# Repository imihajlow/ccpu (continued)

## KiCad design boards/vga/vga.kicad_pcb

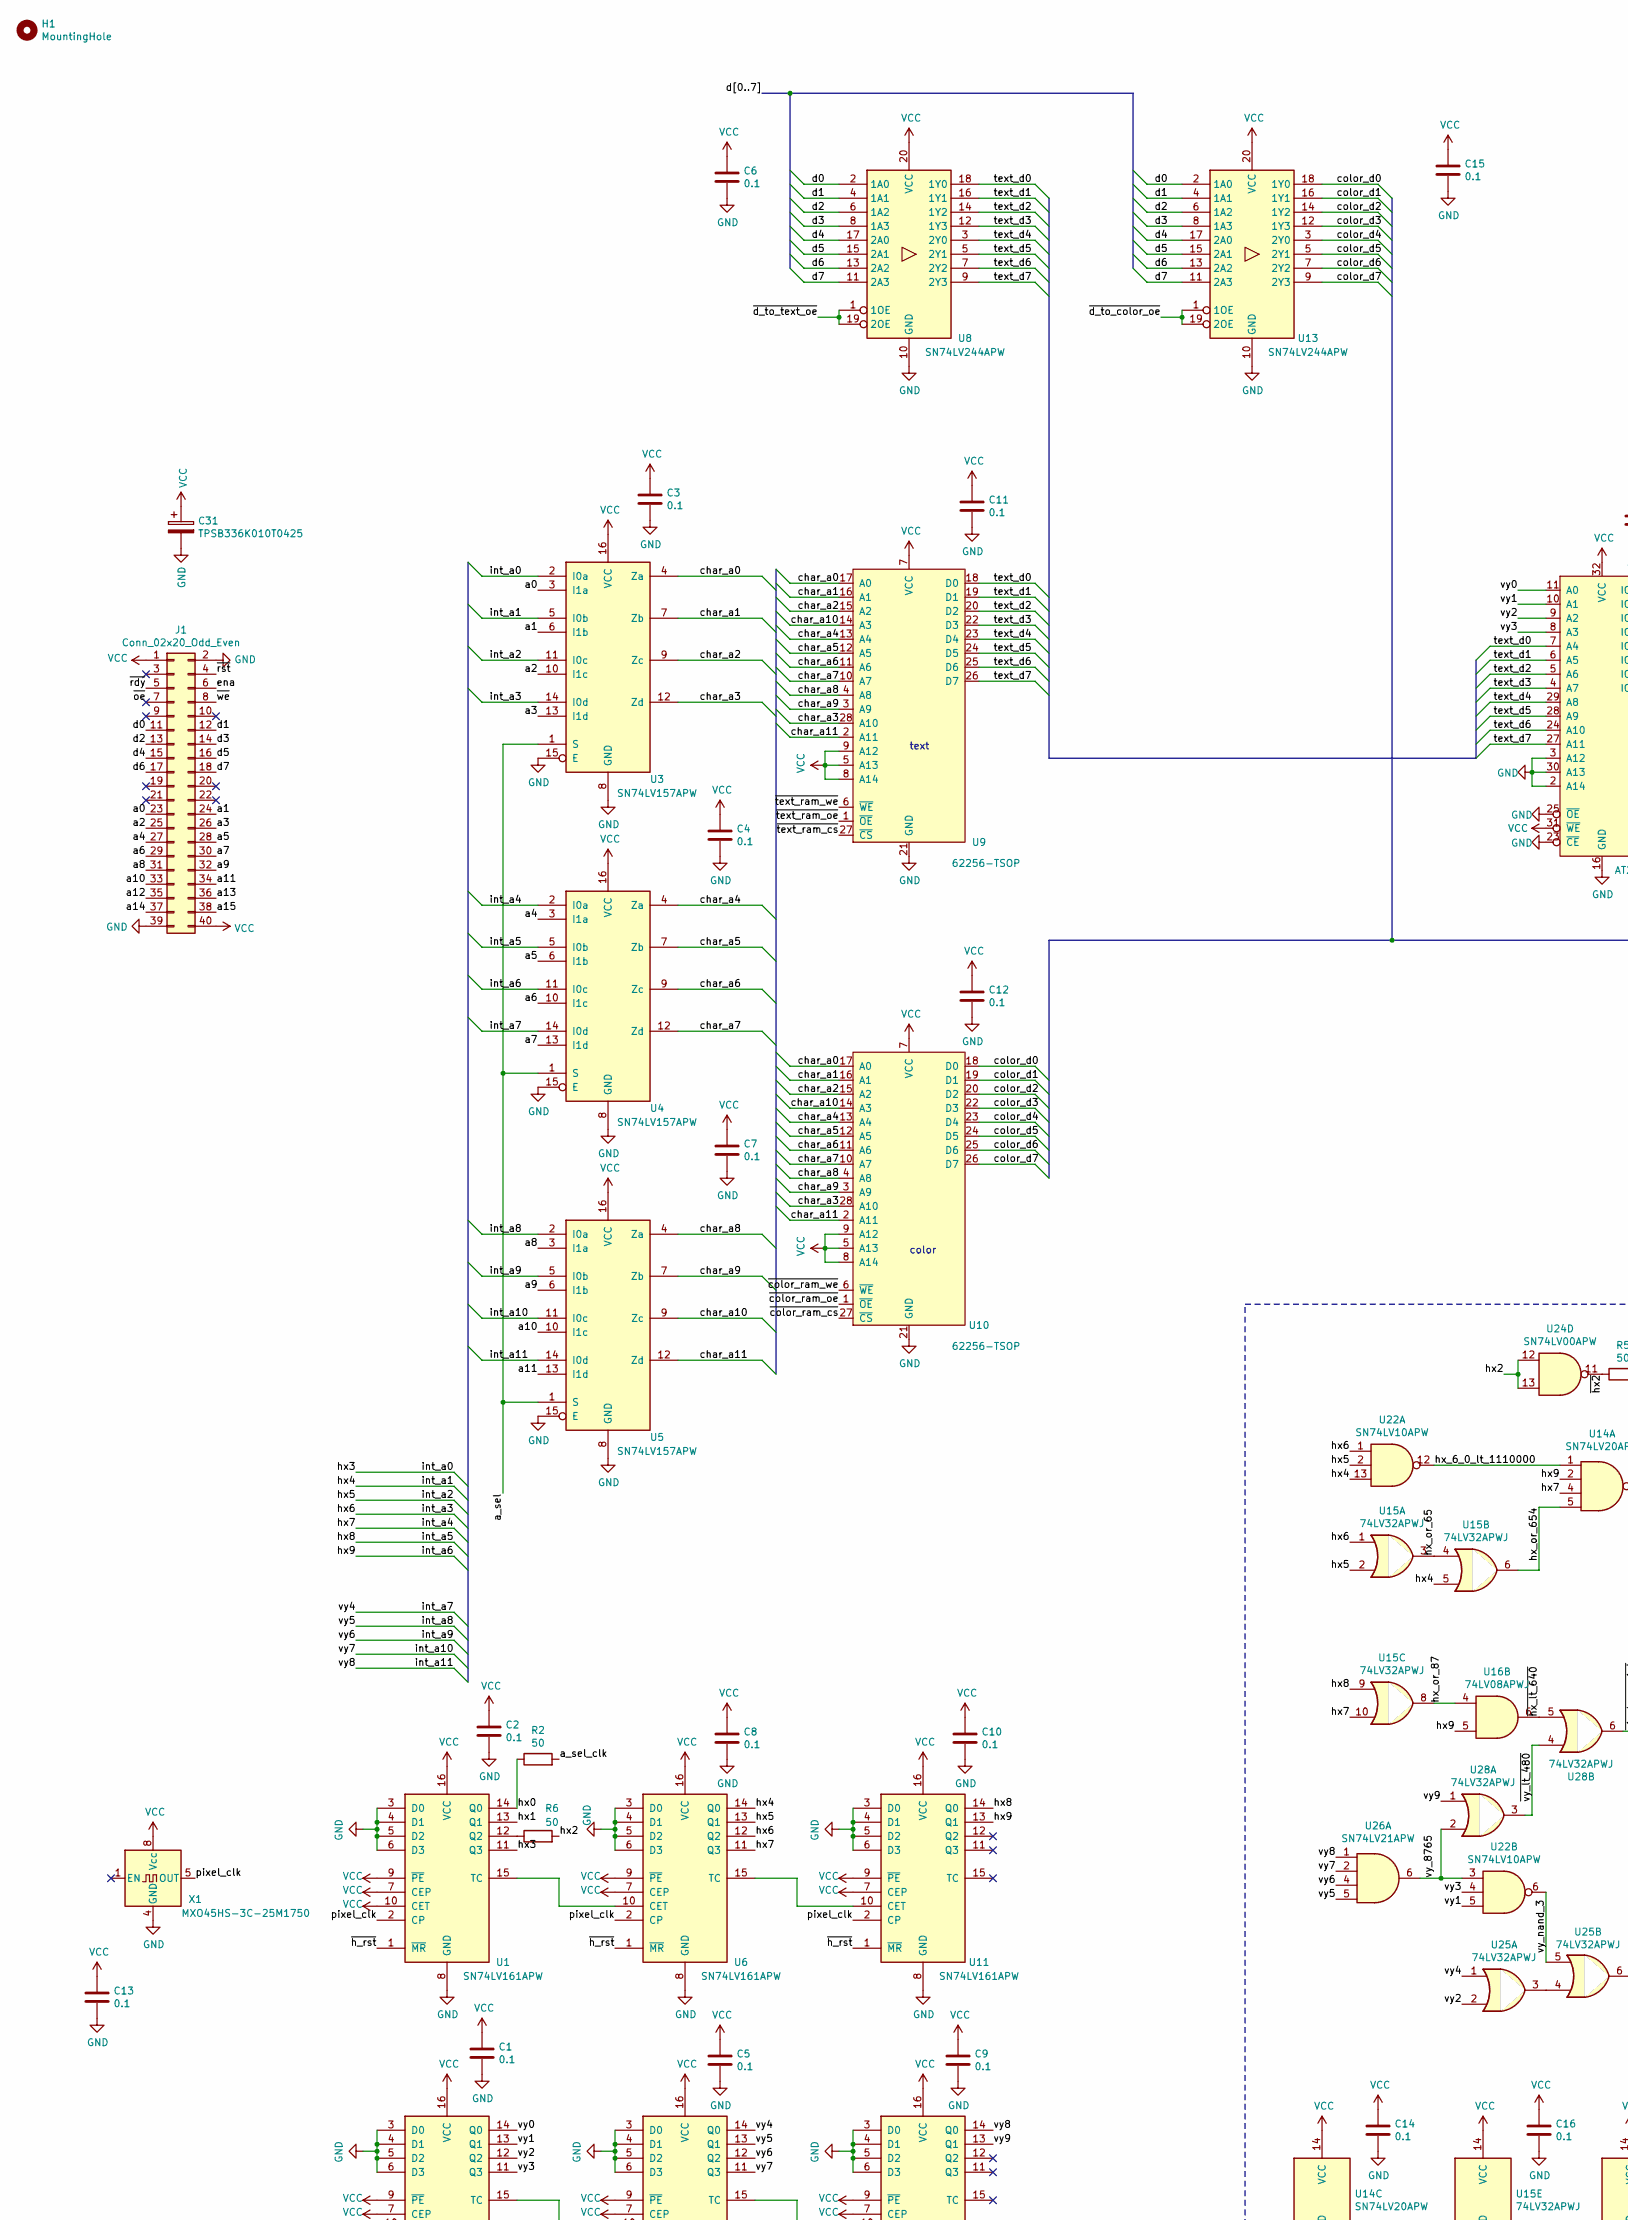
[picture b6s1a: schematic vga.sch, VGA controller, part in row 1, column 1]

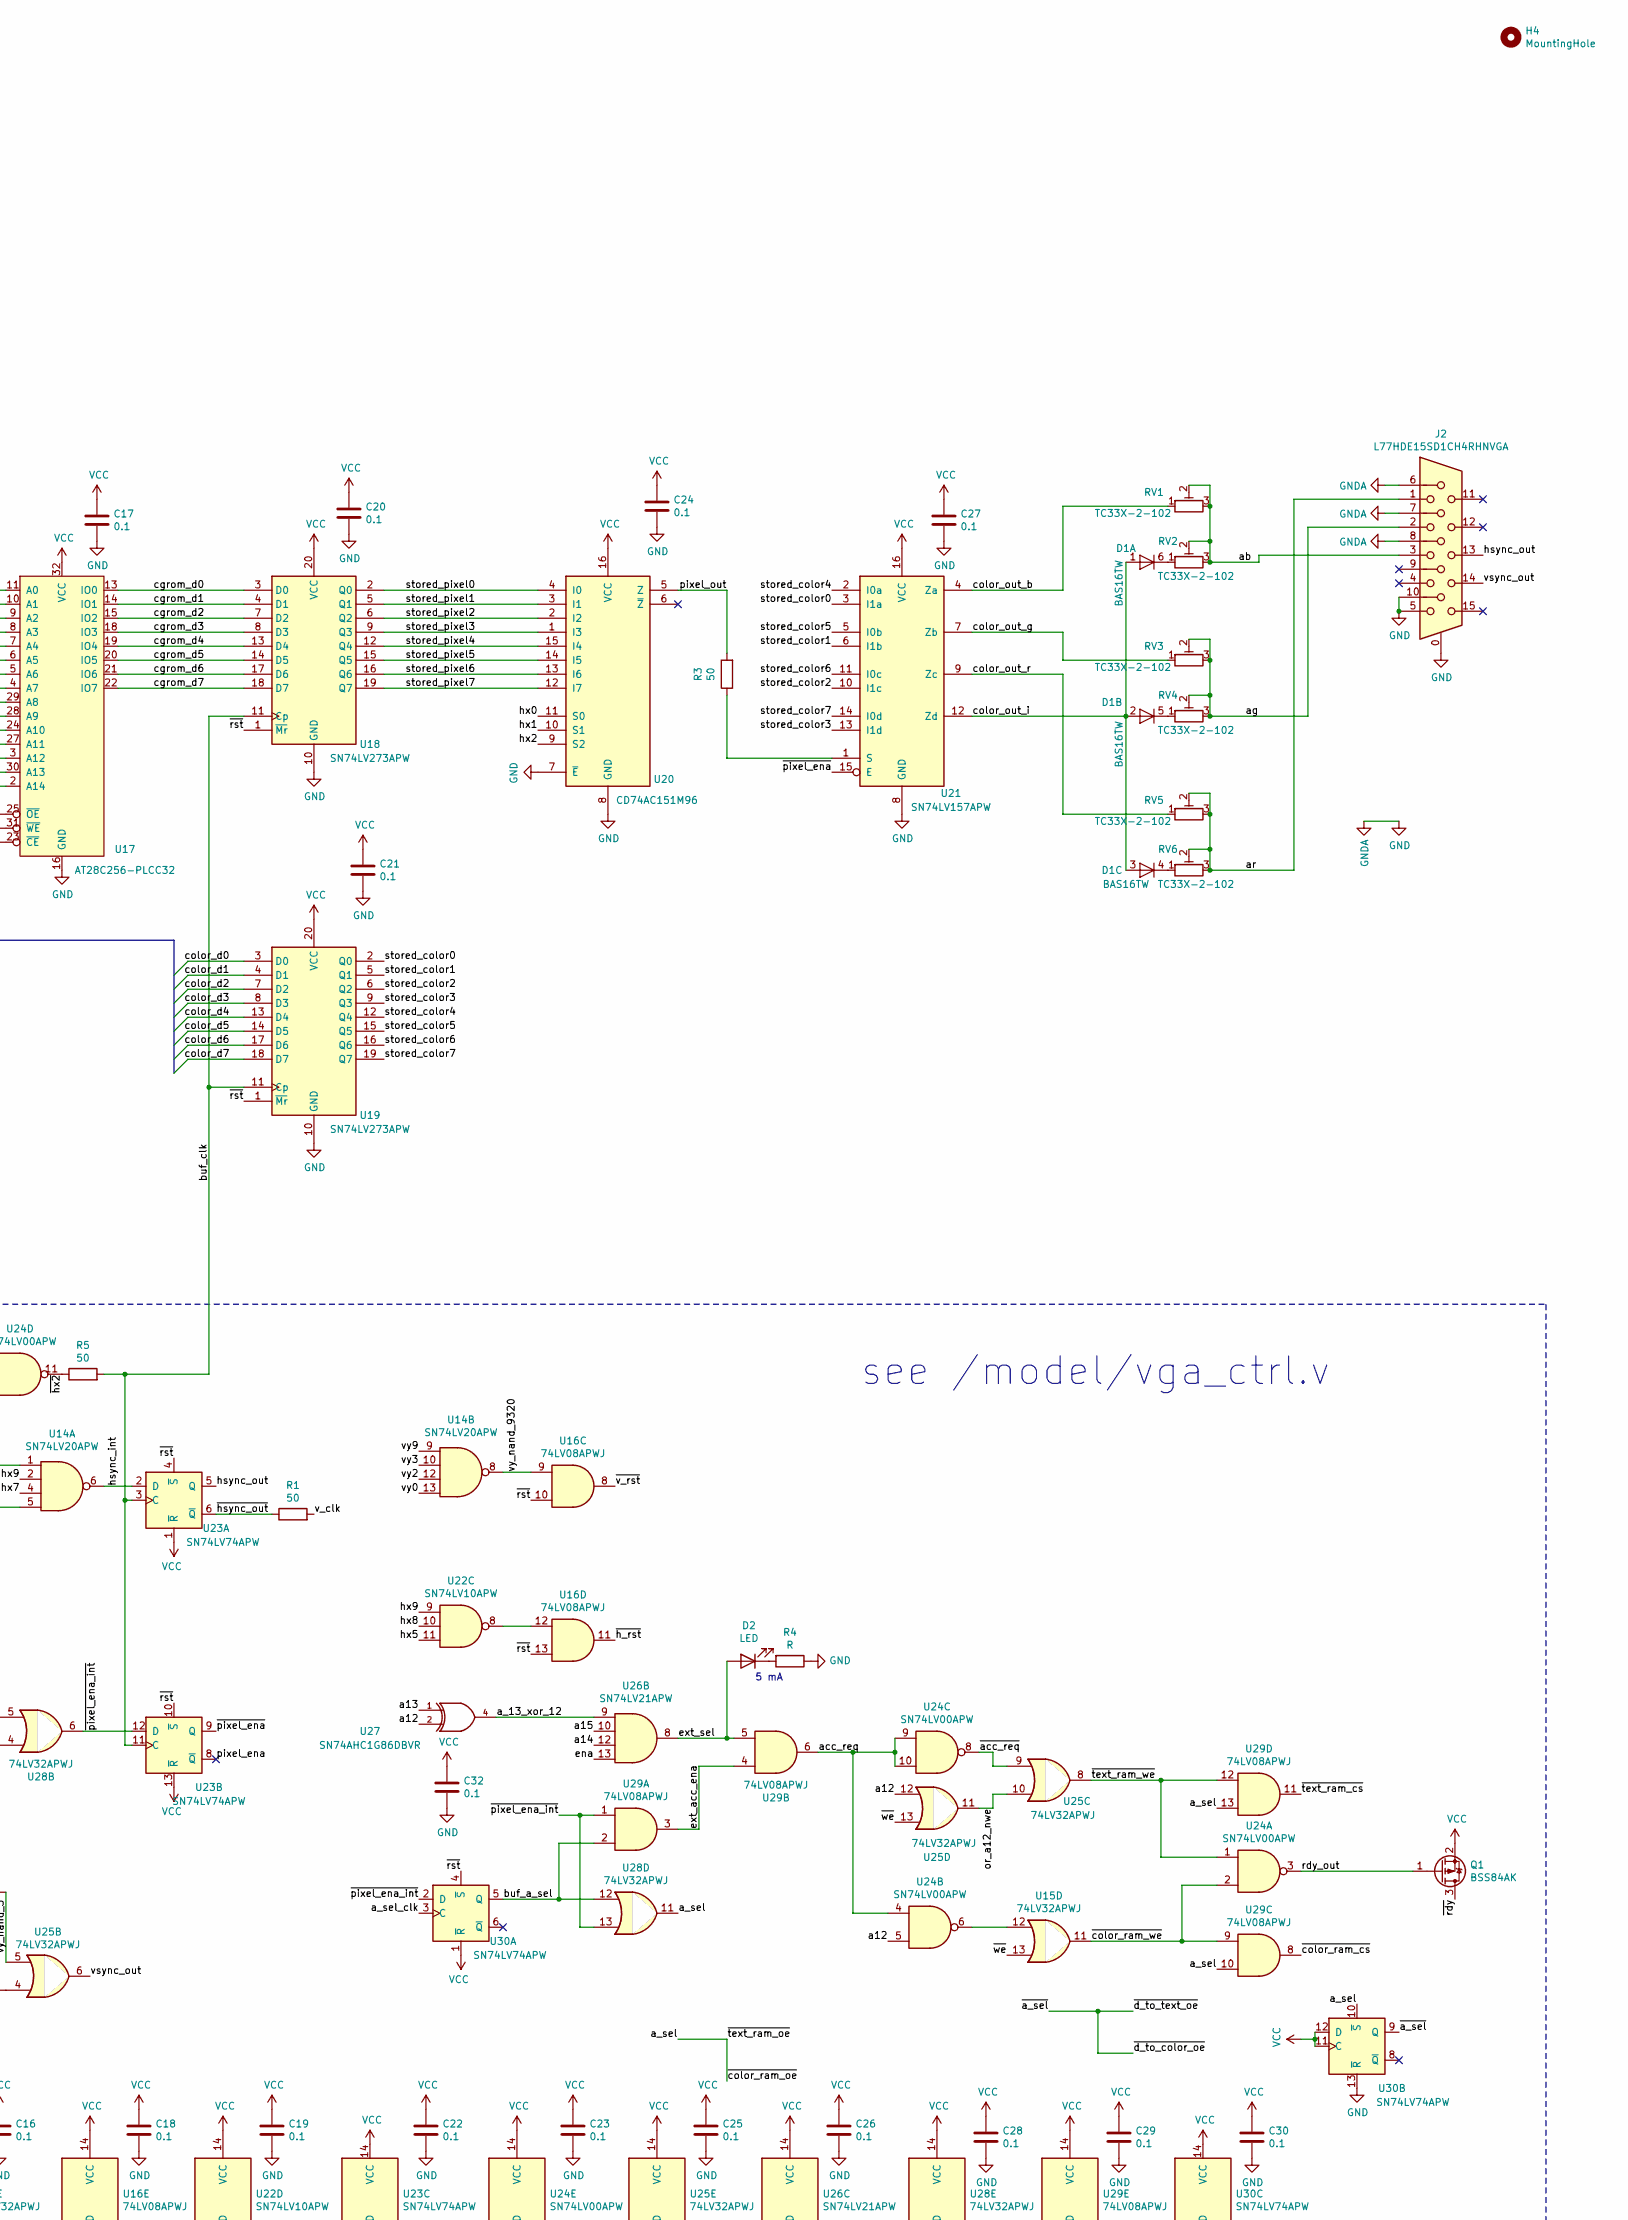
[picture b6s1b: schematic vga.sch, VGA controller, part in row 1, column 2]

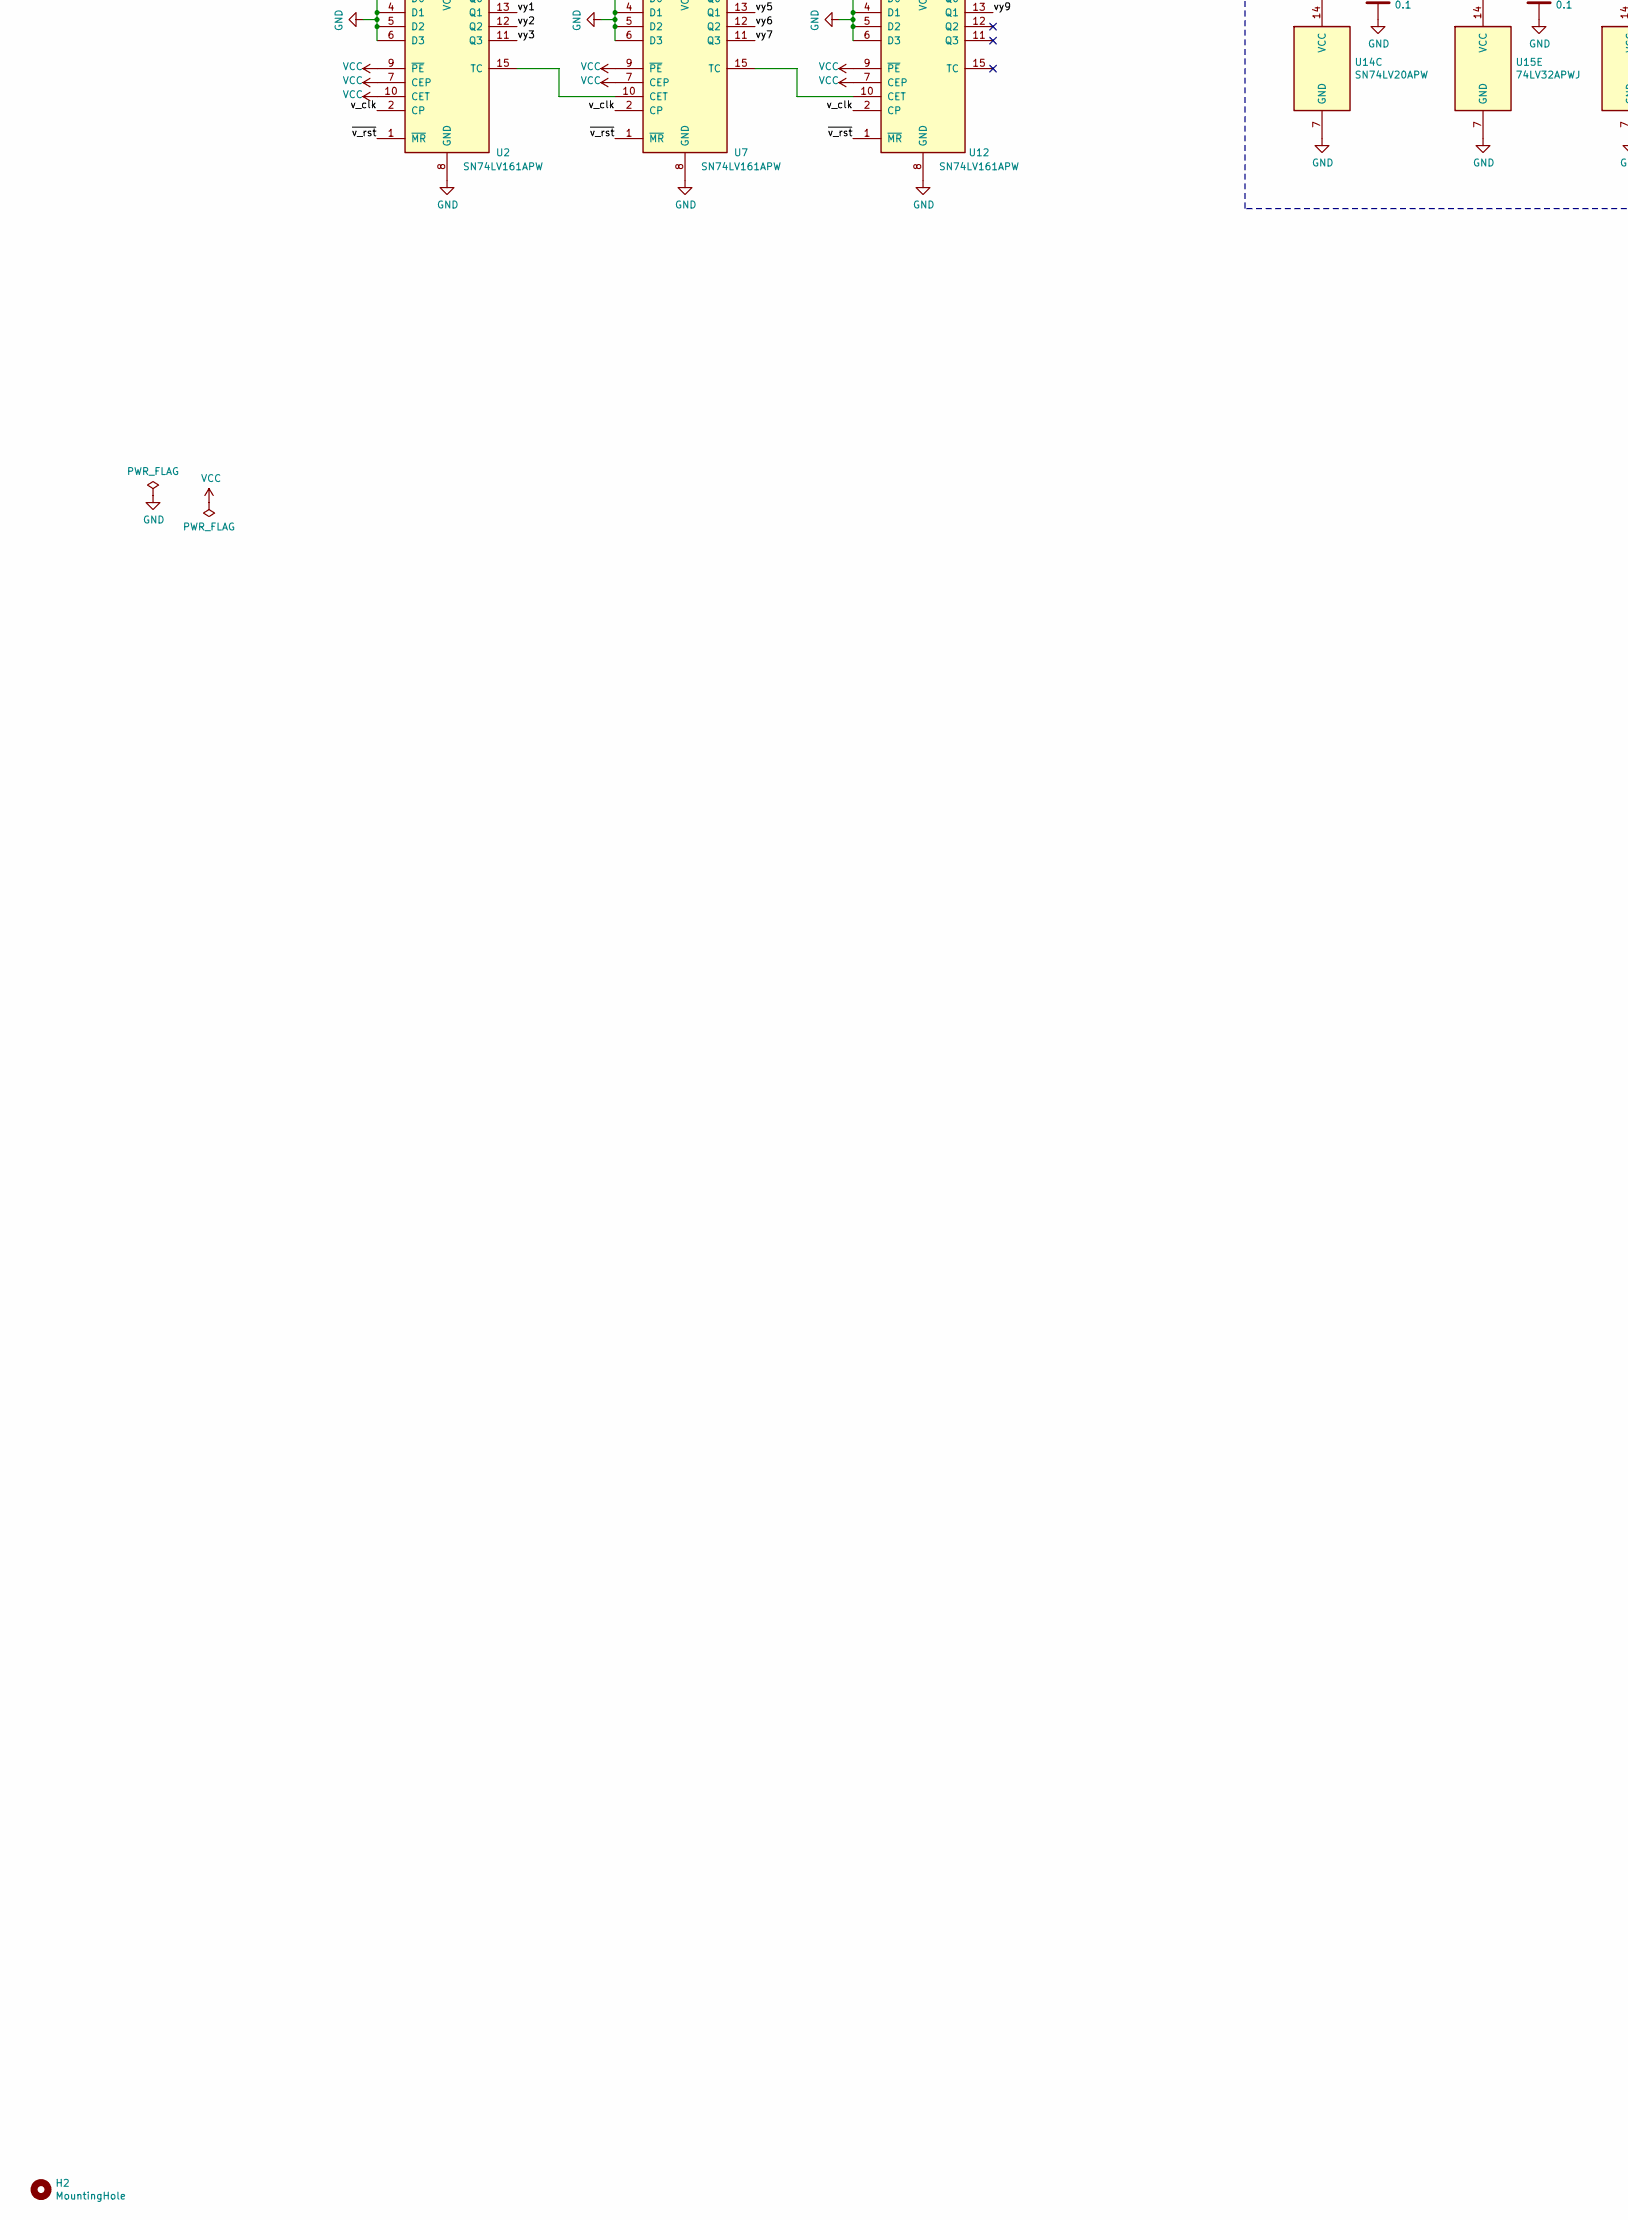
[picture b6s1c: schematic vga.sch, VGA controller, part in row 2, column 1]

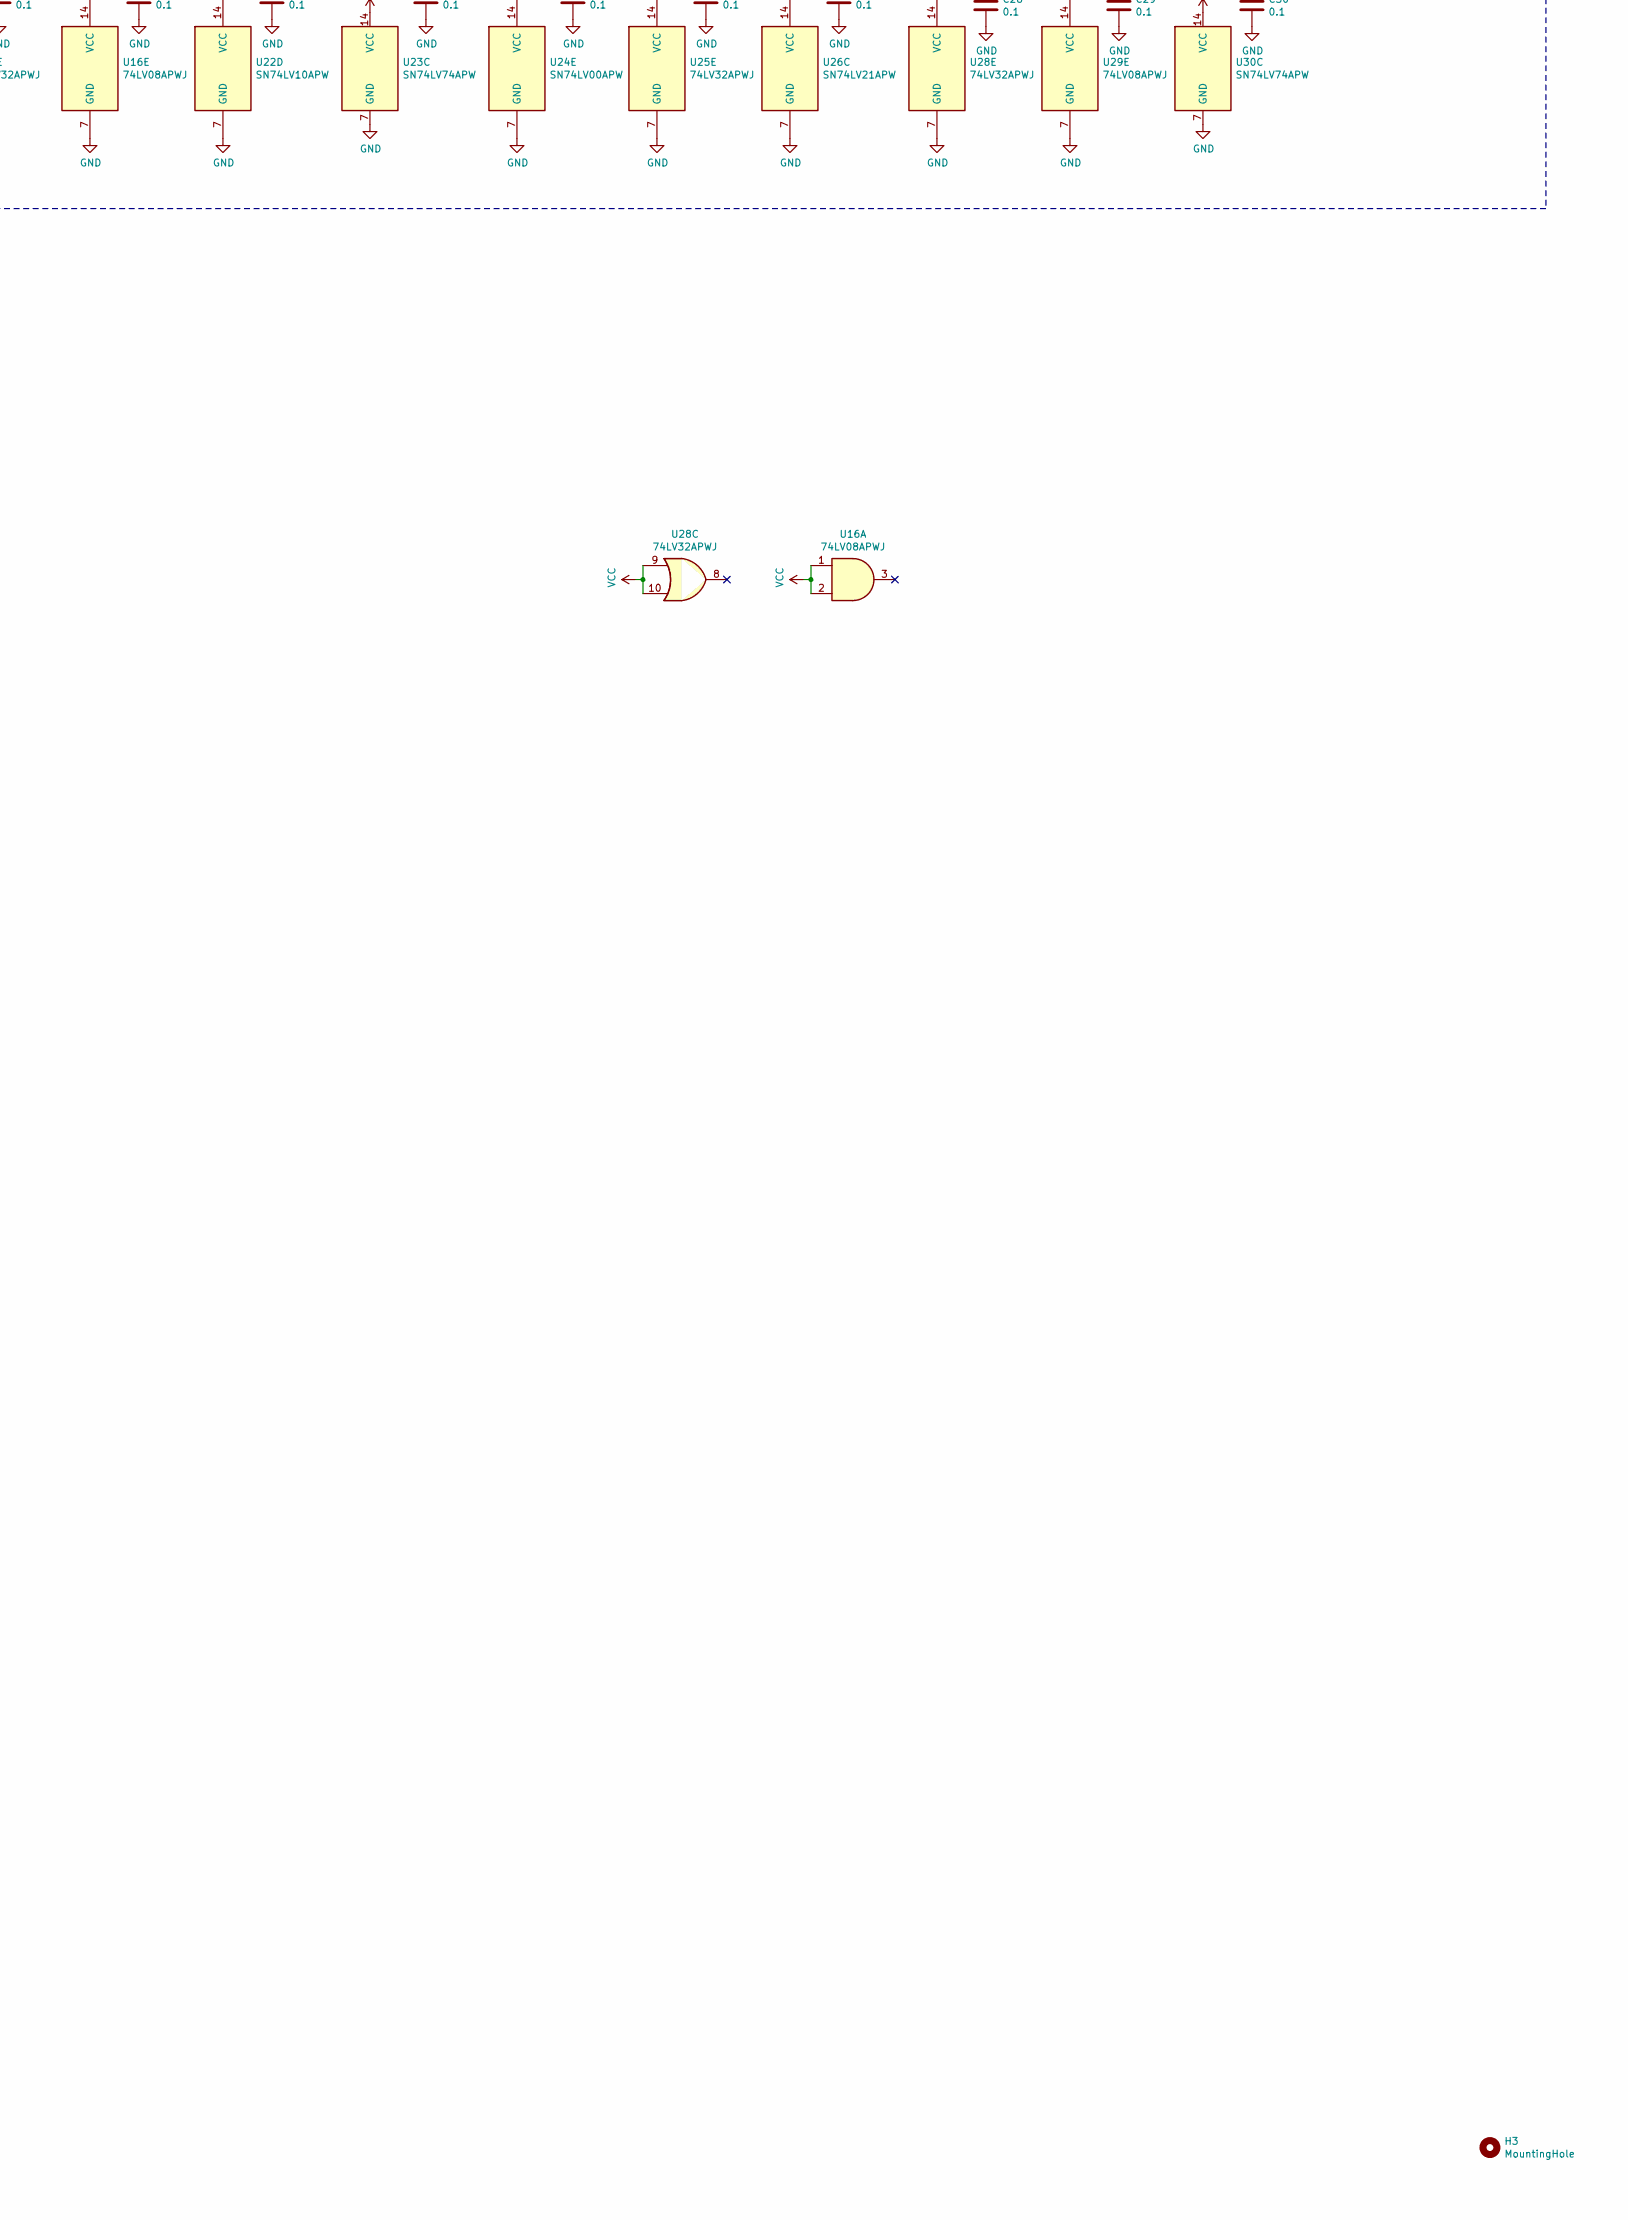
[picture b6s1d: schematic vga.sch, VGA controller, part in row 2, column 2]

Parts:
C1, C2, C3, C4, C5, C6, C7, C8, C9, C10, C11, C12, C13, C14, C15, C16, C17, C18, C19, C20, C21, C22, C23, C24, C25, C26, C27, C28, C29, C30, C32: 0.1; C_0805_2012Metric
C31: TPSB336K010T0425; CP_EIA-3528-15_AVX-H_Pad1.50x2.35mm_HandSolder
D1: BAS16TW; SOT-363_SC-70-6
D2: LED; LED_0805_2012Metric
H1, H2, H3, H4: MountingHole; MountingHole_3.2mm_M3
J1: Conn_02x20_Odd_Even; PinHeader_2x20_P2.54mm_Horizontal
J2: L77HDE15SD1CH4RHNVGA; DSUB-15-HD_Female_Horizontal_P2.29x1.98mm_EdgePinOffset8.35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
Q1: BSS84AK; SOT-23
R1, R2, R3, R5, R6: 50; R_0805_2012Metric
R4: R; R_0805_2012Metric
RV1, RV2, RV3, RV4, RV5, RV6: TC33X-2-102; Potentiometer_Bourns_TC33X_Vertical
U1, U2, U6, U7, U11, U12: SN74LV161APW; TSSOP-16_4.4x5mm_P0.65mm
U3, U4, U5, U21: SN74LV157APW; TSSOP-16_4.4x5mm_P0.65mm
U8, U13: SN74LV244APW; TSSOP-20_4.4x6.5mm_P0.65mm
U9, U10: 62256-TSOP; TSOP-I-28_11.8x8mm_P0.55mm
U14: SN74LV20APW; TSSOP-14_4.4x5mm_P0.65mm
U15, U25, U28: 74LV32APWJ; TSSOP-14_4.4x5mm_P0.65mm
U16, U29: 74LV08APWJ; TSSOP-14_4.4x5mm_P0.65mm
U17: AT28C256-PLCC32; PLCC-32_SMD_Socket
U18, U19: SN74LV273APW; TSSOP-20_4.4x6.5mm_P0.65mm
U20: CD74AC151M96; SOIC-16_3.9x9.9mm_P1.27mm
U22: SN74LV10APW; TSSOP-14_4.4x5mm_P0.65mm
U23, U30: SN74LV74APW; TSSOP-14_4.4x5mm_P0.65mm
U24: SN74LV00APW; TSSOP-14_4.4x5mm_P0.65mm
U26: SN74LV21APW; TSSOP-14_4.4x5mm_P0.65mm
U27: SN74AHC1G86DBVR; SOT-23-5
X1: MXO45HS-3C-25M1750; Oscillator_DIP-8

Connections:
/a0: J1.23, U3.3 (I1a)
/a1: J1.24, U3.6 (I1b)
/a2: J1.25, U3.10 (I1c)
/a3: J1.26, U3.13 (I1d)
/a4: J1.27, U4.3 (I1a)
/a5: J1.28, U4.6 (I1b)
/a6: J1.29, U4.10 (I1c)
/a7: J1.30, U4.13 (I1d)
/a8: J1.31, U5.3 (I1a)
/a9: J1.32, U5.6 (I1b)
/a10: J1.33, U5.10 (I1c)
/a11: J1.34, U5.13 (I1d)
/a12: J1.35, U24.5, U25.12, U27.2
/a13: J1.36, U27.1
/a14: J1.37, U26.12
/a15: J1.38, U26.10
/a_13_xor_12: U26.9, U27.4
/a_sel: U3.1 (S), U4.1 (S), U5.1 (S), U9.1 (~OE), U10.1 (~OE), U28.11, U29.10, U29.13, U30.10 (~S)
/a_sel_clk: R2.2, U30.3 (C)
/ab: J2.3, RV1.2, RV1.3, RV2.2, RV2.3
/acc_req: U24.4, U24.9, U24.10, U29.6
/ag: J2.2, RV3.2, RV3.3, RV4.2, RV4.3
/ar: J2.1, RV5.2, RV5.3, RV6.2, RV6.3
/buf_a_sel: U28.12, U29.2, U30.5 (Q)
/buf_clk: R5.2, U18.11 (Cp), U19.11 (Cp), U23.3 (C), U23.11 (C)
/cgrom_d0: U17.13 (IO0), U18.3 (D0)
/cgrom_d1: U17.14 (IO1), U18.4 (D1)
/cgrom_d2: U17.15 (IO2), U18.7 (D2)
/cgrom_d3: U17.18 (IO3), U18.8 (D3)
/cgrom_d4: U17.19 (IO4), U18.13 (D4)
/cgrom_d5: U17.20 (IO5), U18.14 (D5)
/cgrom_d6: U17.21 (IO6), U18.17 (D6)
/cgrom_d7: U17.22 (IO7), U18.18 (D7)
/char_a0: U3.4 (Za), U9.17 (A0), U10.17 (A0)
/char_a1: U3.7 (Zb), U9.16 (A1), U10.16 (A1)
/char_a2: U3.9 (Zc), U9.15 (A2), U10.15 (A2)
/char_a3: U3.12 (Zd), U9.28 (A10), U10.28 (A10)
/char_a4: U4.4 (Za), U9.13 (A4), U10.13 (A4)
/char_a5: U4.7 (Zb), U9.12 (A5), U10.12 (A5)
/char_a6: U4.9 (Zc), U9.11 (A6), U10.11 (A6)
/char_a7: U4.12 (Zd), U9.10 (A7), U10.10 (A7)
/char_a8: U5.4 (Za), U9.4 (A8), U10.4 (A8)
/char_a9: U5.7 (Zb), U9.3 (A9), U10.3 (A9)
/char_a10: U5.9 (Zc), U9.14 (A3), U10.14 (A3)
/char_a11: U5.12 (Zd), U9.2 (A11), U10.2 (A11)
/color_d0: U10.18 (D0), U13.18 (1Y0), U19.3 (D0)
/color_d1: U10.19 (D1), U13.16 (1Y1), U19.4 (D1)
/color_d2: U10.20 (D2), U13.14 (1Y2), U19.7 (D2)
/color_d3: U10.22 (D3), U13.12 (1Y3), U19.8 (D3)
/color_d4: U10.23 (D4), U13.3 (2Y0), U19.13 (D4)
/color_d5: U10.24 (D5), U13.5 (2Y1), U19.14 (D5)
/color_d6: U10.25 (D6), U13.7 (2Y2), U19.17 (D6)
/color_d7: U10.26 (D7), U13.9 (2Y3), U19.18 (D7)
/color_out_b: RV1.1, U21.4 (Za)
/color_out_g: RV3.1, U21.7 (Zb)
/color_out_i: D1.1 (A), D1.2 (A), D1.3 (A), U21.12 (Zd)
/color_out_r: RV5.1, U21.9 (Zc)
/d0: J1.11, U8.2 (1A0), U13.2 (1A0)
/d1: J1.12, U8.4 (1A1), U13.4 (1A1)
/d2: J1.13, U8.6 (1A2), U13.6 (1A2)
/d3: J1.14, U8.8 (1A3), U13.8 (1A3)
/d4: J1.15, U8.17 (2A0), U13.17 (2A0)
/d5: J1.16, U8.15 (2A1), U13.15 (2A1)
/d6: J1.17, U8.13 (2A2), U13.13 (2A2)
/d7: J1.18, U8.11 (2A3), U13.11 (2A3)
/ena: J1.6, U26.13
/ext_acc_ena: U29.3, U29.4
/ext_sel: D2.2 (A), U26.8, U29.5
/hsync_int: U14.6, U23.2 (D)
/hsync_out: J2.13, U23.5 (Q)
/hx0: R2.1, U1.14 (Q0), U20.11 (S0)
/hx1: U1.13 (Q1), U20.10 (S1)
/hx2: R6.2, U20.9 (S2), U24.12, U24.13
/hx3: U1.11 (Q3), U3.2 (I0a)
/hx4: U3.5 (I0b), U6.14 (Q0), U15.5, U22.13
/hx5: U3.11 (I0c), U6.13 (Q1), U15.2, U22.2, U22.11
/hx6: U3.14 (I0d), U6.12 (Q2), U15.1, U22.1
/hx7: U4.2 (I0a), U6.11 (Q3), U14.4, U15.10
/hx8: U4.5 (I0b), U11.14 (Q0), U15.9, U22.10
/hx9: U4.11 (I0c), U11.13 (Q1), U14.2, U16.5, U22.9
/hx_6_0_lt_1110000: U14.1, U22.12
/hx_or_65: U15.3, U15.4
/hx_or_87: U15.8, U16.4
/hx_or_654: U14.5, U15.6
/int_a7: U4.14 (I0d), U7.14 (Q0), U25.1
/int_a8: U5.2 (I0a), U7.13 (Q1), U26.5
/int_a9: U5.5 (I0b), U7.12 (Q2), U26.4
/int_a10: U5.11 (I0c), U7.11 (Q3), U26.2
/int_a11: U5.14 (I0d), U12.14 (Q0), U26.1
/or_a12_nwe: U25.10, U25.11
/pixel_clk: U1.2 (CP), U6.2 (CP), U11.2 (CP), X1.5 (OUT)
/pixel_out: R3.2, U20.5 (Z)
/rdy_out: Q1.1 (G), U24.3
/stored_color0: U19.2 (Q0), U21.3 (I1a)
/stored_color1: U19.5 (Q1), U21.6 (I1b)
/stored_color2: U19.6 (Q2), U21.10 (I1c)
/stored_color3: U19.9 (Q3), U21.13 (I1d)
/stored_color4: U19.12 (Q4), U21.2 (I0a)
/stored_color5: U19.15 (Q5), U21.5 (I0b)
/stored_color6: U19.16 (Q6), U21.11 (I0c)
/stored_color7: U19.19 (Q7), U21.14 (I0d)
/stored_pixel0: U18.2 (Q0), U20.4 (I0)
/stored_pixel1: U18.5 (Q1), U20.3 (I1)
/stored_pixel2: U18.6 (Q2), U20.2 (I2)
/stored_pixel3: U18.9 (Q3), U20.1 (I3)
/stored_pixel4: U18.12 (Q4), U20.15 (I4)
/stored_pixel5: U18.15 (Q5), U20.14 (I5)
/stored_pixel6: U18.16 (Q6), U20.13 (I6)
/stored_pixel7: U18.19 (Q7), U20.12 (I7)
/text_d0: U8.18 (1Y0), U9.18 (D0), U17.7 (A4)
/text_d1: U8.16 (1Y1), U9.19 (D1), U17.6 (A5)
/text_d2: U8.14 (1Y2), U9.20 (D2), U17.5 (A6)
/text_d3: U8.12 (1Y3), U9.22 (D3), U17.4 (A7)
/text_d4: U8.3 (2Y0), U9.23 (D4), U17.29 (A8)
/text_d5: U8.5 (2Y1), U9.24 (D5), U17.28 (A9)
/text_d6: U8.7 (2Y2), U9.25 (D6), U17.24 (A10)
/text_d7: U8.9 (2Y3), U9.26 (D7), U17.27 (A11)
/v_clk: R1.2, U2.2 (CP), U7.2 (CP), U12.2 (CP)
/vsync_out: J2.14, U25.6
/vy0: U2.14 (Q0), U14.13, U17.11 (A0)
/vy1: U2.13 (Q1), U17.10 (A1), U22.5
/vy2: U2.12 (Q2), U14.12, U17.9 (A2), U25.2
/vy3: U2.11 (Q3), U14.10, U17.8 (A3), U22.4
/vy9: U12.13 (Q1), U14.9, U28.1
/vy_8765: U22.3, U26.6, U28.2
/vy_nand_3: U22.6, U25.5
/vy_nand_9320: U14.8, U16.9
/~a_sel: U8.1 (1OE), U8.19 (2OE), U13.1 (1OE), U13.19 (2OE), U30.9 (Q)
/~acc_req: U24.8, U25.9
/~color_ram_cs: U10.27 (~CS), U29.8
/~color_ram_we: U10.6 (~WE), U15.11, U24.2, U29.9
/~h_rst: U1.1 (~MR), U6.1 (~MR), U11.1 (~MR), U16.11
/~hsync_out: R1.1, U23.6 (~Q)
/~hx2: R5.1, U24.11
/~hx_lt_640: U16.6, U28.5
/~pixel_ena: U21.15 (E), U23.9 (Q)
/~pixel_ena_int: U23.12 (D), U28.6, U28.13, U29.1, U30.2 (D)
/~rdy: J1.5, Q1.3 (D)
/~rst: J1.4, U16.10, U16.13, U18.1 (~Mr), U19.1 (~Mr), U23.4 (~S), U23.10 (~S), U30.4 (~S)
/~text_ram_cs: U9.27 (~CS), U29.11
/~text_ram_we: U9.6 (~WE), U24.1, U25.8, U29.12
/~v_rst: U2.1 (~MR), U7.1 (~MR), U12.1 (~MR), U16.8
/~vy_lt_480: U28.3, U28.4
/~we: J1.8, U15.13, U25.13
GND: C1.2, C2.2, C3.2, C4.2, C5.2, C6.2, C7.2, C8.2, C9.2, C10.2, C11.2, C12.2, C13.2, C14.2, C15.2, C16.2, C17.2, C18.2, C19.2, C20.2, C21.2, C22.2, C23.2, C24.2, C25.2, C26.2, C27.2, C28.2, C29.2, C30.2, C31.2, C32.2, J1.2, J1.39, J2.0, J2.5, J2.6, J2.7, J2.8, J2.10, R4.1, U1.3 (D0), U1.4 (D1), U1.5 (D2), U1.6 (D3), U1.8 (GND), U2.3 (D0), U2.4 (D1), U2.5 (D2), U2.6 (D3), U2.8 (GND), U3.8 (GND), U3.15 (E), U4.8 (GND), U4.15 (E), U5.8 (GND), U5.15 (E), U6.3 (D0), U6.4 (D1), U6.5 (D2), U6.6 (D3), U6.8 (GND), U7.3 (D0), U7.4 (D1), U7.5 (D2), U7.6 (D3), U7.8 (GND), U8.10 (GND), U9.21 (GND), U10.21 (GND), U11.3 (D0), U11.4 (D1), U11.5 (D2), U11.6 (D3), U11.8 (GND), U12.3 (D0), U12.4 (D1), U12.5 (D2), U12.6 (D3), U12.8 (GND), U13.10 (GND), U14.7 (GND), U15.7 (GND), U16.7 (GND), U17.2 (A14), U17.3 (A12), U17.16 (GND), U17.23 (~CE), U17.25 (~OE), U17.30 (A13), U18.10 (GND), U19.10 (GND), U20.7 (~E), U20.8 (GND), U21.8 (GND), U22.7 (GND), U23.7 (GND), U24.7 (GND), U25.7 (GND), U26.7 (GND), U27.3 (GND), U28.7 (GND), U29.7 (GND), U30.7 (GND), U30.13 (~R), X1.4 (GND)
unnamed: D1.4 (K), RV6.1
unnamed: D1.5 (K), RV4.1
unnamed: D1.6 (K), RV2.1
unnamed: D2.1 (K), R4.2
unnamed: R3.1, U21.1 (S)
unnamed: R6.1, U1.12 (Q2)
unnamed: U1.15 (TC), U6.10 (CET)
unnamed: U2.15 (TC), U7.10 (CET)
unnamed: U6.15 (TC), U11.10 (CET)
unnamed: U7.15 (TC), U12.10 (CET)
unnamed: U15.12, U24.6
unnamed: U16.12, U22.8
unnamed: U25.3, U25.4
VCC: C1.1, C2.1, C3.1, C4.1, C5.1, C6.1, C7.1, C8.1, C9.1, C10.1, C11.1, C12.1, C13.1, C14.1, C15.1, C16.1, C17.1, C18.1, C19.1, C20.1, C21.1, C22.1, C23.1, C24.1, C25.1, C26.1, C27.1, C28.1, C29.1, C30.1, C31.1, C32.1, J1.1, J1.40, Q1.2 (S), U1.7 (CEP), U1.9 (~PE), U1.10 (CET), U1.16 (VCC), U2.7 (CEP), U2.9 (~PE), U2.10 (CET), U2.16 (VCC), U3.16 (VCC), U4.16 (VCC), U5.16 (VCC), U6.7 (CEP), U6.9 (~PE), U6.16 (VCC), U7.7 (CEP), U7.9 (~PE), U7.16 (VCC), U8.20 (VCC), U9.5 (A13), U9.7 (VCC), U9.8 (A14), U9.9 (A12), U10.5 (A13), U10.7 (VCC), U10.8 (A14), U10.9 (A12), U11.7 (CEP), U11.9 (~PE), U11.16 (VCC), U12.7 (CEP), U12.9 (~PE), U12.16 (VCC), U13.20 (VCC), U14.14 (VCC), U15.14 (VCC), U16.1, U16.2, U16.14 (VCC), U17.31 (~WE), U17.32 (VCC), U18.20 (VCC), U19.20 (VCC), U20.16 (VCC), U21.16 (VCC), U22.14 (VCC), U23.1 (~R), U23.13 (~R), U23.14 (VCC), U24.14 (VCC), U25.14 (VCC), U26.14 (VCC), U27.5 (VCC), U28.9, U28.10, U28.14 (VCC), U29.14 (VCC), U30.1 (~R), U30.11 (C), U30.12 (D), U30.14 (VCC), X1.8 (Vcc)

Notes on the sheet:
text
color
see /model/vga_ctrl.v
5 mA
